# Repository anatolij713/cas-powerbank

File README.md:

# Powerbank with Flashlight for Metabo/CAS 18V Battery pack

## Required materials:
- "MH-KC24" DC-DC Step-Down Module
- Star type 20mm diameter Aluminium PCB with 1W LED
- Assembled Flashlight Board
- 2 pcs 1208YD Buttons
- 4 pcs Insert nuts M4x6mm
- 4 Screws M4x16
- 2 Springs about 6mm length and 4..6mm diameter
- 2 male Crimp Terminals 6.35x0.8mm
- Wires
- Some Glue:)

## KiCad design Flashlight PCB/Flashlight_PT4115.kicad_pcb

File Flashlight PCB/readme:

Gerber.zip file can be used for PCB ordering at JLCPCB or another service.
Flashlight_PT4115-F_Cu.pdf or Flashlight_PT4115-F_Cu.svg - for homemade PCB, images are mirrored.

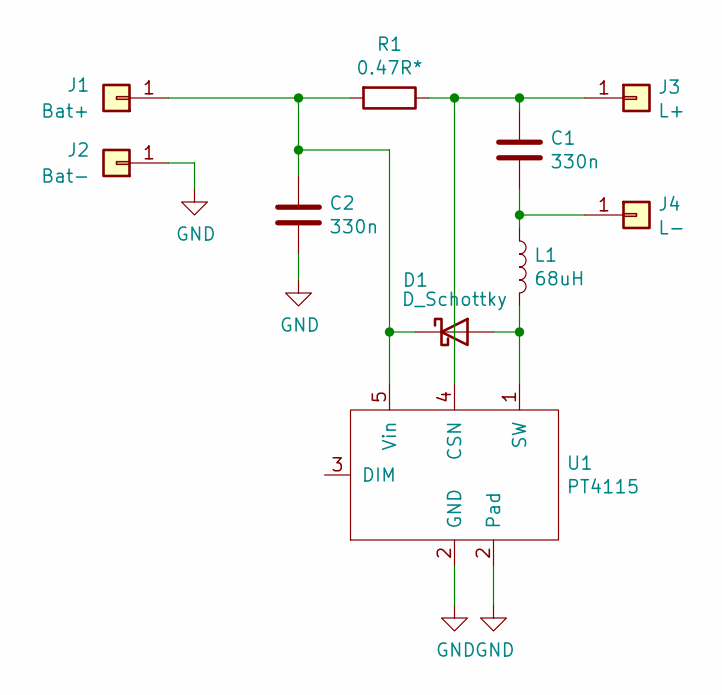
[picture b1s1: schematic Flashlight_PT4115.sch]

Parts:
C1, C2: 330n; C_0805_2012Metric
D1: D_Schottky; D_SMA
J1: Bat+; TestPoint_THTPad_3.0x3.0mm_Drill1.5mm
J2: Bat-; TestPoint_THTPad_3.0x3.0mm_Drill1.5mm
J3: L+; TestPoint_THTPad_3.0x3.0mm_Drill1.5mm
J4: L-; TestPoint_THTPad_3.0x3.0mm_Drill1.5mm
L1: 68uH; L_Radial_D8.7mm_P5.00mm_Fastron_07HCP
R1: 0.47R*; R_Axial_DIN0207_L6.3mm_D2.5mm_P7.62mm_Horizontal
U1: PT4115; SOT-89-5

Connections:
GND: C2.2, J2.1, U1.2 (GND)
unnamed: C1.1, J3.1, R1.1, U1.4 (CSN)
unnamed: C1.2, J4.1, L1.1
unnamed: C2.1, D1.1 (K), J1.1, R1.2, U1.5 (Vin)
unnamed: D1.2 (A), L1.2, U1.1 (SW)

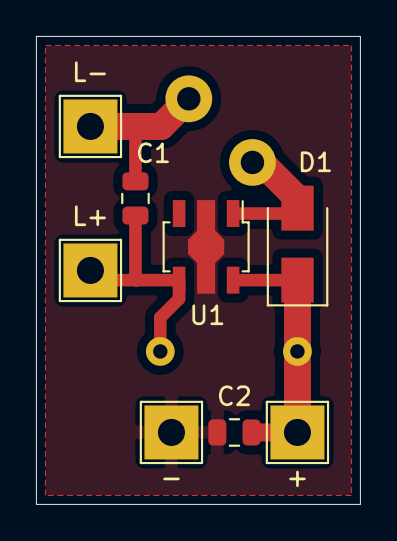
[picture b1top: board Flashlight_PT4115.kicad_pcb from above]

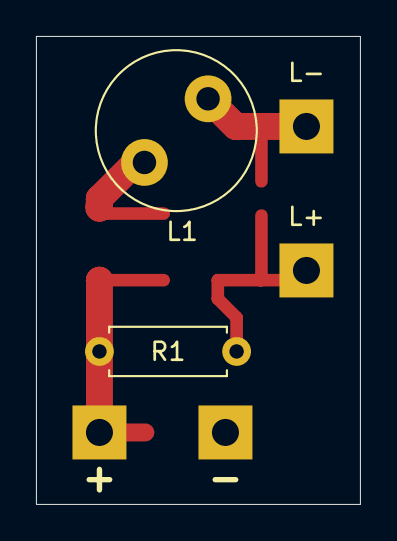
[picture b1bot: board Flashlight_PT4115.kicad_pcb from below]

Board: 2 copper layers, 18.0 x 26.0 mm, 10 parts (2 on the bottom side), 5 nets.

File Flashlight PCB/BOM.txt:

C1, C2  SMD 0805 capacitors             330nF .. 1uF, 50V
D1      SMD SMA Package Shottkey Diode  SS14 or another
L1      THT Inductor, min 300mA         68uH, for example, Bourns RLB0914-680KL
U1      Led Driver IC                   PT4115
